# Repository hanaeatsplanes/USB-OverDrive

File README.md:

# USB OverDrive
> youll never need another dongle

## What even is this??

This is a USB-C -> 3x USB-A hub!

This uses:
* TUSB4041l as the main Hub
* 3x LP5912 as an LDO
* A male USB-C plug (JAE DX07P024AJ1) no need to worry about cables

## Why does this exist??

**This project was funded by [Hack Club Outpost](https://outpost.hackclub.com)!**

As a MacBook user, I deseperately need a dongle. I decided to design my own Hack Club themed dongle!

## Images

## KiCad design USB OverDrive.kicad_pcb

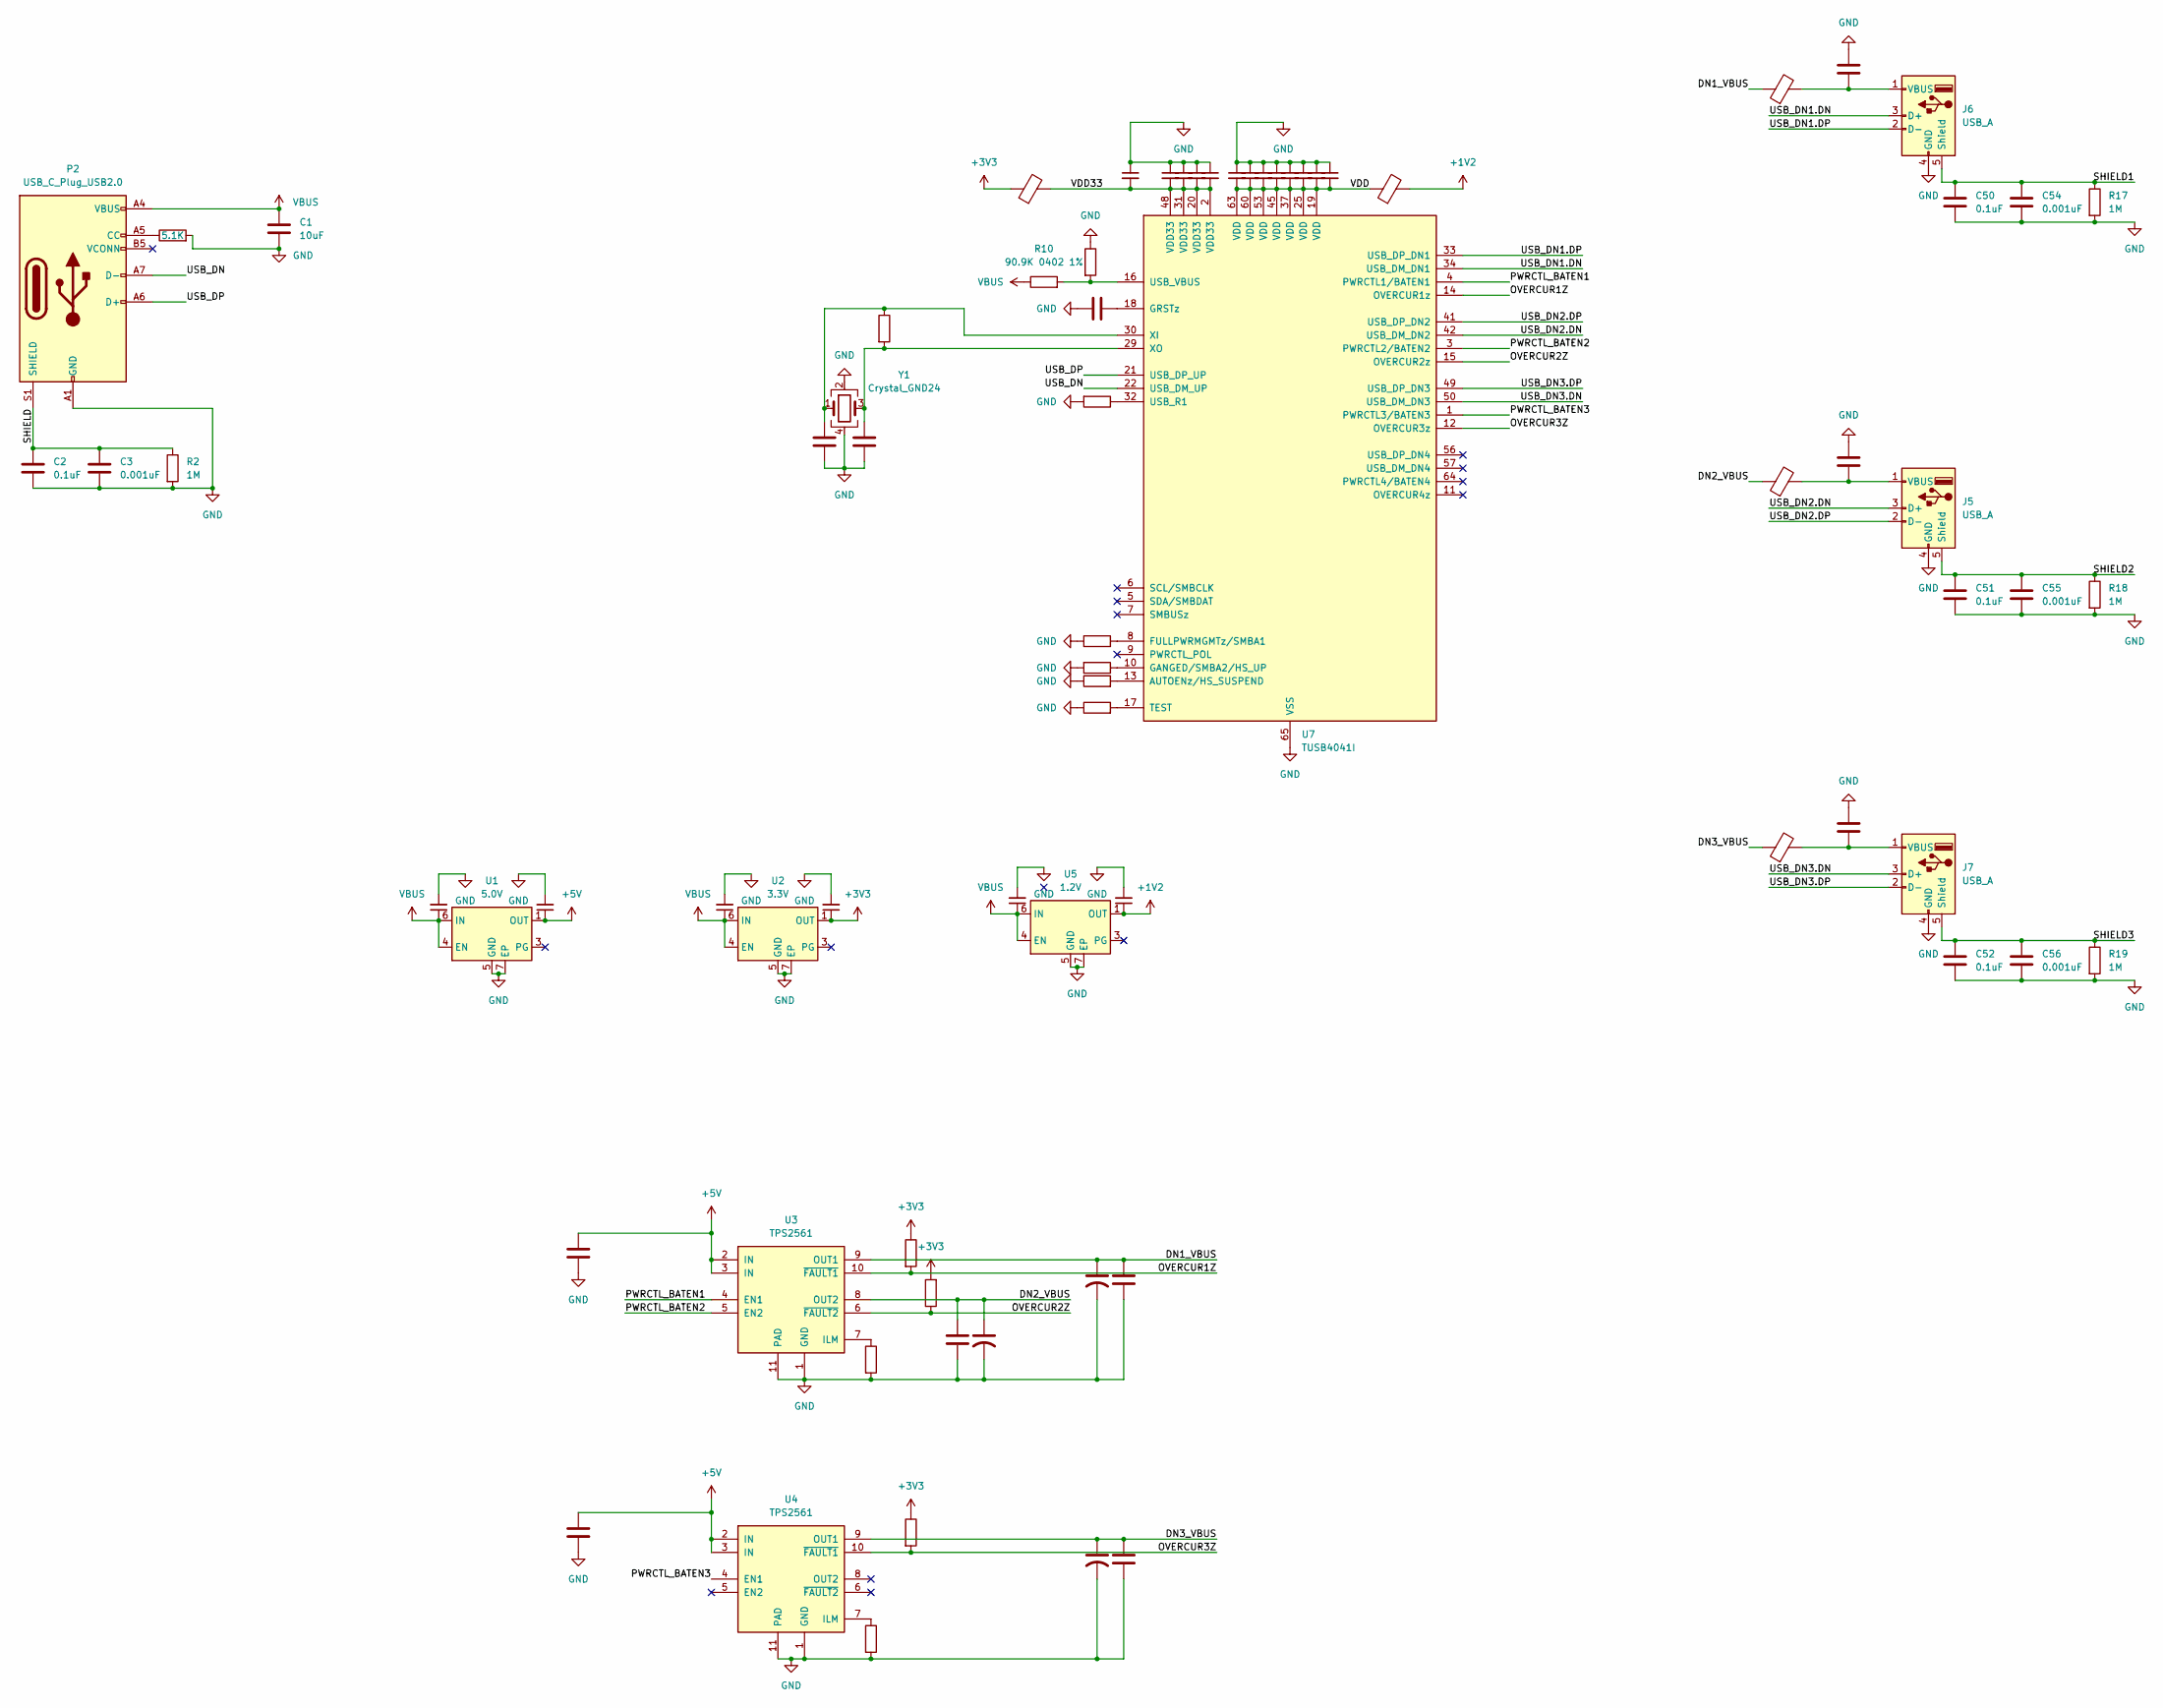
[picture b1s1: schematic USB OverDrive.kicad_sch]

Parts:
C1, C25, C37: 10uF; C_0402_1005Metric
C2, C8, C9, C14, C16, C17, C26, C27, C28, C29, C30, C31, C32, C33, C34, C35, C36, C38, C39, C40, C50, C51, C52: 0.1uF; C_0402_1005Metric
C3, C54, C55, C56: 0.001uF; C_0402_1005Metric
C4, C7, C10, C12, C22, C23, C24: 1uF; C_0402_1005Metric
C11, C13: 18pF; C_0402_1005Metric
C18, C20, C21: 150uF; C_1206_3216Metric
FB1, FB2, FB3, FB4, FB5: 220 @ 100 MHz; L_0201_0603Metric
J5, J6, J7: USB_A; USB-A-TH_C42622
P2: USB_C_Plug_USB2.0; USB_C_Plug_JAE_DX07P024AJ1
R1: 5.1K; R_0402_1005Metric
R2, R3, R17, R18, R19: 1M; R_0402_1005Metric
R4, R5: 25.5K 0402 5%; R_0402_1005Metric
R6, R7, R8: 10K 0402 5%; R_0402_1005Metric
R10: 90.9K 0402 1%; R_0402_1005Metric
R11: 10K 0402 1%; R_0402_1005Metric
R12: 9.53K 0402 1%; R_0402_1005Metric
R13, R14, R15: 4.7K 0402 5%; R_0402_1005Metric
R16: 4.7K; R_0402_1005Metric
U1: 5.0V; WSON-6-1EP_2x2mm_P0.65mm_EP1x1.6mm_ThermalVias
U2: 3.3V; WSON-6-1EP_2x2mm_P0.65mm_EP1x1.6mm_ThermalVias
U3, U4: TPS2561; VSON-10-1EP_3x3mm_P0.5mm_EP1.65x2.4mm_ThermalVias
U5: 1.2V; WSON-6-1EP_2x2mm_P0.65mm_EP1x1.6mm_ThermalVias
U7: TUSB4041I; HTQFP-64-1EP_10x10mm_P0.5mm_EP8x8mm_Mask4.4x4.4mm_ThermalVi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
Y1: Crystal_GND24; Crystal_SMD_3225-4Pin_3.2x2.5mm

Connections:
+1V2: C24.1, FB2.2, U5.1 (OUT)
+5V: C7.1, C8.1, C9.1, U1.1 (OUT), U3.2 (IN), U3.3 (IN), U4.2 (IN), U4.3 (IN)
/DN1_VBUS: C16.1, C20.1, FB3.1, U3.9 (OUT1)
/DN2_VBUS: C17.1, C21.1, FB4.1, U3.8 (OUT2)
/DN3_VBUS: C14.1, C18.1, FB5.1, U4.9 (OUT1)
/OVERCUR2Z: R7.1, U3.6 (~FAULT2), U7.15 (OVERCUR2z)
/OVERCUR3Z: R8.2, U4.10 (~FAULT1), U7.12 (OVERCUR3z)
/PWRCTL_BATEN1: U3.4 (EN1), U7.4 (PWRCTL1/BATEN1)
/PWRCTL_BATEN2: U3.5 (EN2), U7.3 (PWRCTL2/BATEN2)
/PWRCTL_BATEN3: U4.4 (EN1), U7.1 (PWRCTL3/BATEN3)
/SHIELD: C2.1, C3.1, P2.S1 (SHIELD), R2.1
/SHIELD1: C50.1, C54.1, J6.5 (Shield), R17.1
/SHIELD2: C51.1, C55.1, J5.5 (Shield), R18.1
/SHIELD3: C52.1, C56.1, J7.5 (Shield), R19.1
/USB_DN: P2.A7 (D-), U7.22 (USB_DM_UP)
/USB_DN1.DN: J6.3 (D+), U7.34 (USB_DM_DN1)
/USB_DN1.DP: J6.2 (D-), U7.33 (USB_DP_DN1)
/USB_DN2.DN: J5.3 (D+), U7.42 (USB_DM_DN2)
/USB_DN2.DP: J5.2 (D-), U7.41 (USB_DP_DN2)
/USB_DN3.DN: J7.3 (D+), U7.50 (USB_DM_DN3)
/USB_DN3.DP: J7.2 (D-), U7.49 (USB_DP_DN3)
/USB_DP: P2.A6 (D+), U7.21 (USB_DP_UP)
/VDD: C30.2, C31.2, C32.2, C33.2, C34.2, C35.2, C36.2, C37.2, FB2.1, U7.19 (VDD), U7.25 (VDD), U7.37 (VDD), U7.45 (VDD), U7.53 (VDD), U7.60 (VDD), U7.63 (VDD)
/VDD33: C25.2, C26.2, C27.2, C28.2, C29.2, FB1.2, U7.2 (VDD33), U7.20 (VDD33), U7.31 (VDD33), U7.48 (VDD33)
GND: C1.2, C2.2, C3.2, C4.2, C7.2, C8.2, C9.2, C10.2, C11.1, C12.2, C13.1, C14.2, C16.2, C17.2, C18.2, C20.2, C21.2, C22.2, C23.1, C24.2, C25.1, C26.1, C27.1, C28.1, C29.1, C30.1, C31.1, C32.1, C33.1, C34.1, C35.1, C36.1, C37.1, C38.1, C39.1, C40.1, C50.2, C51.2, C52.2, C54.2, C55.2, C56.2, J5.4 (GND), J6.4 (GND), J7.4 (GND), P2.A1 (GND), P2.A12 (GND), P2.B1 (GND), P2.B12 (GND), R1.2, R2.2, R4.2, R5.2, R11.1, R12.2, R13.1, R14.1, R15.1, R16.2, R17.2, R18.2, R19.2, U1.5 (GND), U1.7 (EP), U2.5 (GND), U2.7 (EP), U3.1 (GND), U3.11 (PAD), U4.1 (GND), U4.11 (PAD), U5.5 (GND), U5.7 (EP), U7.65 (VSS), Y1.2, Y1.4
unnamed: C39.2, FB4.2, J5.1 (VBUS)
unnamed: C38.2, FB3.2, J6.1 (VBUS)
unnamed: C40.2, FB5.2, J7.1 (VBUS)
unnamed: P2.A5 (CC), R1.1
unnamed: R4.1, U3.7 (ILM)
unnamed: R5.1, U4.7 (ILM)
unnamed: R13.2, U7.13 (AUTOENz/HS_SUSPEND)
unnamed: R15.2, U7.8 (FULLPWRMGMTz/SMBA1)
unnamed: R16.1, U7.10 (GANGED/SMBA2/HS_UP)
unnamed: C23.2, U7.18 (GRSTz)
unnamed: R14.2, U7.17 (TEST)
unnamed: R12.1, U7.32 (USB_R1)
unnamed: R10.2, R11.2, U7.16 (USB_VBUS)
unnamed: C11.2, R3.1, U7.30 (XI), Y1.1
unnamed: C13.2, R3.2, U7.29 (XO), Y1.3
VBUS: C1.1, C4.1, C10.1, C22.1, P2.A4 (VBUS), P2.A9 (VBUS), P2.B4 (VBUS), P2.B9 (VBUS), R10.1, U1.4 (EN), U1.6 (IN), U2.4 (EN), U2.6 (IN), U5.4 (EN), U5.6 (IN)

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
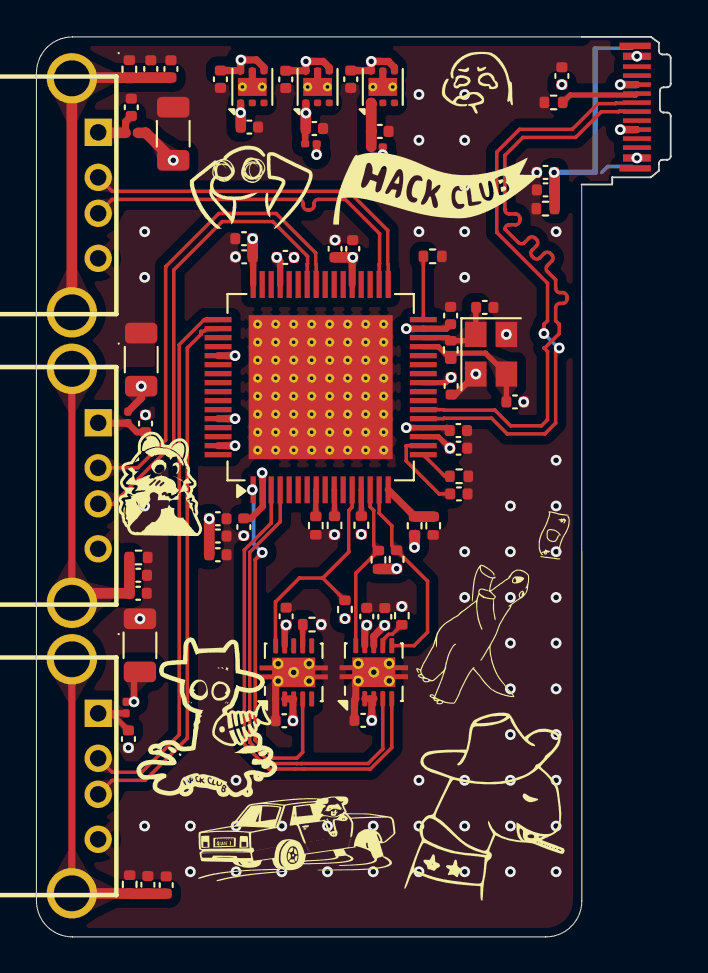
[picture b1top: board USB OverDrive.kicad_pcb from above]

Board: 4 copper layers, 35.2 x 50.0 mm, 76 parts (0 on the bottom side), 43 nets.

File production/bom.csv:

Designator,Footprint,Quantity,Value,LCSC Part #
"C1, C25, C37",0402,3,10uF,
"C10, C12, C22, C23, C24, C4, C7",0402,7,1uF,
"C11, C13",0402,2,18pF,
"C14, C16, C17, C2, C26, C27, C28, C29, C30, C31, C32, C33, C34, C35, C36, C38, C39, C40, C50, C51, C52, C8, C9",0402,23,0.1uF,
"C18, C20, C21",1206,3,150uF,
"C3, C54, C55, C56",0402,4,0.001uF,
"FB1, FB2, FB3, FB4, FB5",0201,5,220 @ 100 MHz,
"J5, J6, J7",USB-A-TH_C42622,3,USB_A,C42622
P2,USB_C_Plug_JAE_DX07P024AJ1,1,USB_C_Plug_USB2.0,
R1,0402,1,5.1K,
R10,0402,1,90.9K 0402 1%,
R11,0402,1,10K 0402 1%,
R12,0402,1,9.53K 0402 1%,
"R13, R14, R15",0402,3,4.7K 0402 5%,
R16,0402,1,4.7K,
"R17, R18, R19, R2, R3",0402,5,1M,
"R4, R5",0402,2,25.5K 0402 5%,
"R6, R7, R8",0402,3,10K 0402 5%,
U1,WSON-6-1EP_2x2mm_P0.65mm_EP1x1.6mm_ThermalVias,1,5.0V,
U2,WSON-6-1EP_2x2mm_P0.65mm_EP1x1.6mm_ThermalVias,1,3.3V,
"U3, U4",VSON-10-1EP_3x3mm_P0.5mm_EP1.65x2.4mm_ThermalVias,2,TPS2561,
U5,WSON-6-1EP_2x2mm_P0.65mm_EP1x1.6mm_ThermalVias,1,1.2V,
U7,HTQFP-64-1EP_10x10mm_P0.5mm_EP8x8mm_Mask4.4x4.4mm_ThermalVias,1,TUSB4041I,
Y1,Crystal_SMD_3225-4Pin_3.2x2.5mm,1,Crystal_GND24,

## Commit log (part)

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2026-06-02 init
